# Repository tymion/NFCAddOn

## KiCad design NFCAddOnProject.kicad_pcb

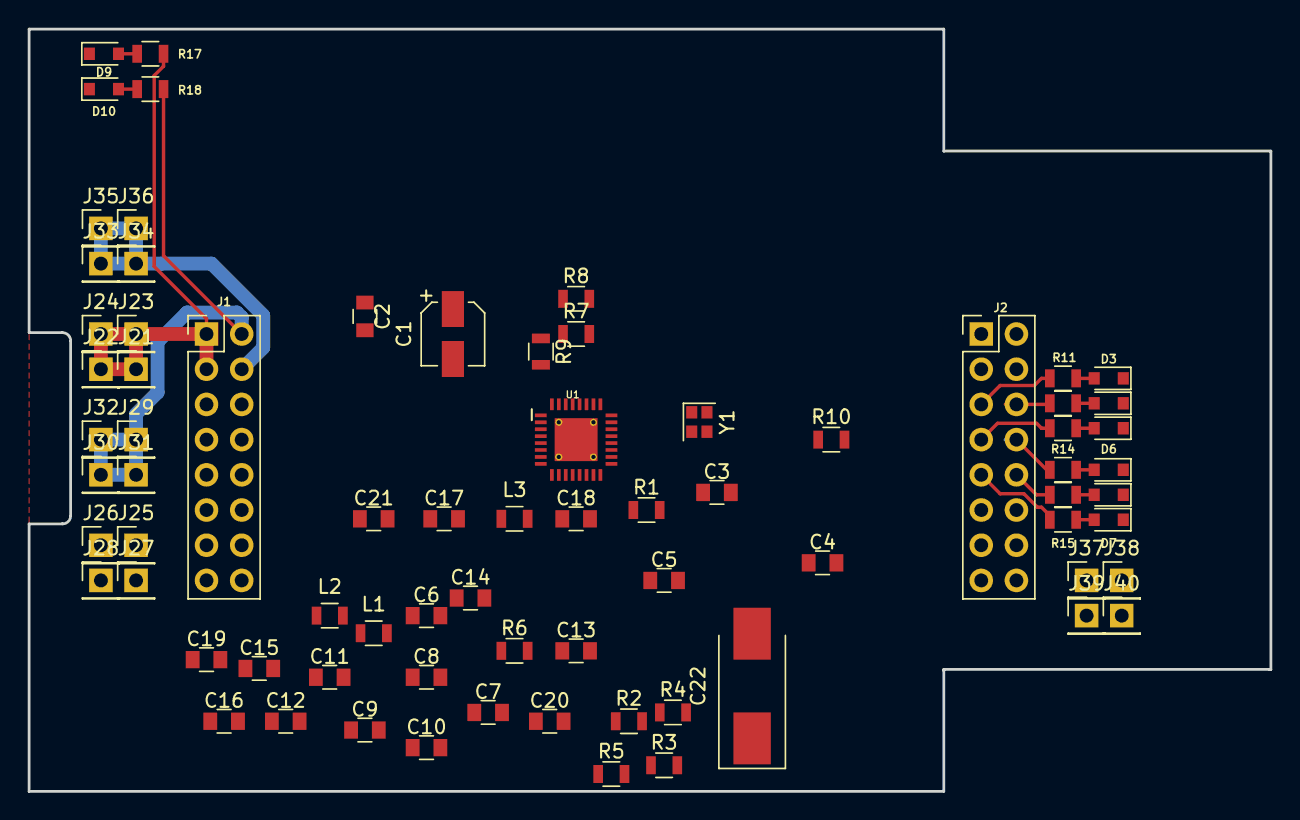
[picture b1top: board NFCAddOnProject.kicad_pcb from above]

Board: 2 copper layers, 89.6 x 55.0 mm, 75 parts (0 on the bottom side), 33 nets.

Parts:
C1: 10uF/25V; CP_Elec_4x5.3
C2, C3, C17, C21: 100nF; C_0805
C4, C5, C13, C14: 100pF; C_0805
C6: 1nF; C_0805
C7, C8: 56pF; C_0805
C9, C12: 12pF; C_0805
C10, C11: 33pF; C_0805
C15, C16: 39pF; C_0805
C18: 1uF; C_0805
C19, C20: 18pF; C_0805
C22: 100uF/10V; CP_Tantalum_Case-D_EIA-7343-31_Hand
D3, D6, D9: KPT-2012EC; D_0805
D4, D7, D10: KPT-2012SGC; D_0805
D5, D8: OSB50805C1E; D_0805
J1: CONN_02X08_L; Pin_Header_Straight_2x08_Pitch2.54mm
J2: CONN_02X08_R; Pin_Header_Straight_2x08_Pitch2.54mm
J21, J22, J23, J24, J25, J26, J27, J28, J29, J30, J31, J32, J33, J34, J35, J36, J37, J38, J39, J40: CONN_01X01; Pin_Header_Straight_1x01_Pitch2.54mm
L1, L2: 470nH; L_0805
L3: 22nH; L_0805
R1: 1K; R_0805
R2: 2.7K; R_0805
R3, R4, R5, R6: 4R42; R_0805
R7, R8, R9: 10K; R_0805
R10, R11: 0; R_0805
R12, R13, R14, R15, R16, R17, R18: 330R; R_0805
U1: PN5120A0HN1/C2.151; SOT-617-1
Y1: 27.12MHz; Crystal_SMD_2016-4pin_2.0x1.6mm

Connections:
+3V3: J33.1, J34.1, J35.1, J36.1
+5V: J21.1, J22.1, J23.1, J24.1, R17.1
GND: C1.2, C2.2, C3.2, C4.1, C5.2, C7.1, C8.2, C13.1, C14.2, C15.1, C16.2, C17.2, C18.2, C19.2, C20.2, C21.2, C22.2, D3.1, D4.1, D5.1, D6.1, D7.1, D8.1, D9.1, D10.1, J1.13, J1.14, J1.15, J2.13, J2.14, J2.15, J2.16, J25.1, J26.1, J27.1, J28.1, J37.1, J38.1, J39.1, J40.1, R10.2, R11.2, U1.1, U1.4, U1.5, U1.10, U1.14, U1.18, U1.25, U1.26, U1.27, U1.28, U1.33
IRQ: J2.5, U1.23
MISO: J2.4, U1.31
MOSI: J2.2, U1.30
NRSTPD: J2.7, R9.2, U1.6
unnamed: C6.1, R1.2, U1.17
unnamed: C6.2, R2.2
unnamed: C4.2, C7.2, C9.1, C10.1, L1.1
unnamed: C9.2, C10.2, C13.2, C15.2, R3.1, R4.1
unnamed: C5.1, C8.1, C11.1, C12.1, L2.1, R2.1
unnamed: C11.2, C12.2, C14.1, C16.1, R5.2, R6.2
unnamed: C19.1, U1.22, Y1.1
unnamed: C20.1, U1.21, Y1.2
unnamed: D4.2, R12.2
unnamed: D5.2, R13.2
unnamed: D6.2, R14.2
unnamed: D7.2, R15.2
unnamed: D8.2, R16.2
unnamed: D9.2, R17.2
unnamed: D10.2, R18.2
unnamed: R3.2, R4.2
unnamed: R5.1, R6.1
unnamed: L1.2, U1.11
unnamed: L2.2, U1.13
unnamed: R10.1, U1.20
unnamed: R11.1, U1.19
SCLK: J2.1, R7.2, U1.29
TVDD: C17.1, C18.1, L3.2, U1.12
VDD: C1.1, C2.1, C21.1, C22.1, J1.4, J29.1, J30.1, J31.1, J32.1, L3.1, R7.1, R8.1, R9.1, R18.1, U1.2, U1.3, U1.9, U1.15, U1.32
VMID: C3.1, R1.1, U1.16
~SS: J2.3, R8.2, U1.24

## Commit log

2018-04-09 First commit for NFC AddOn project
2018-04-11 Adding NFCAddOn project
2018-04-12 Antenna modifications
2018-04-13 Adding MuxPi-AddOn connector
2018-04-17 Finalizing project
2018-05-10 Use other library
2018-05-10 Update schematic
2018-05-11 Update to new version
